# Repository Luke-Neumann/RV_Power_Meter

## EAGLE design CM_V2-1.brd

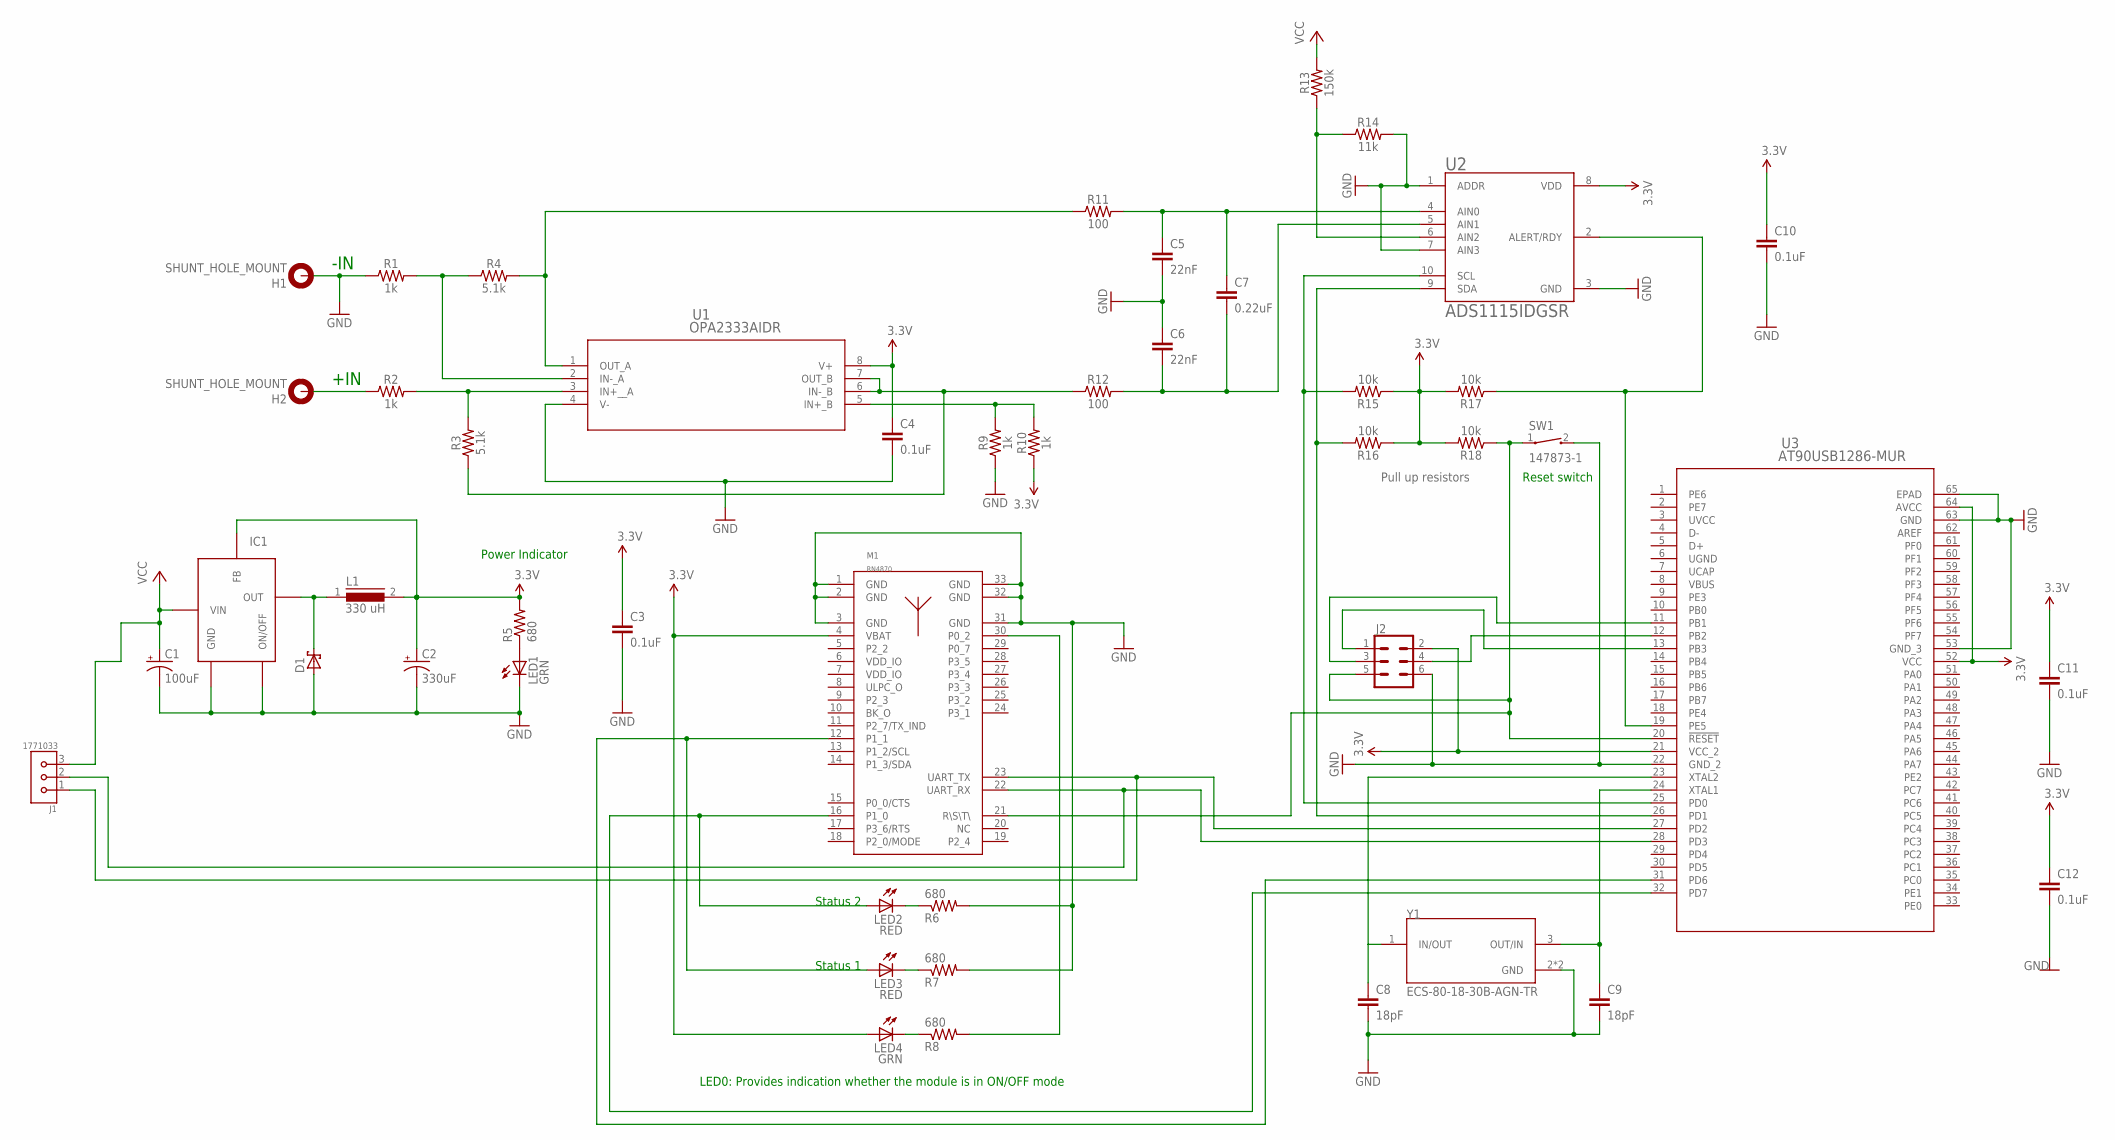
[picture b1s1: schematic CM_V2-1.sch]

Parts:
C1: 100uF; F_CAP; DIGIKEY# PCE3917CT-ND
C2: 330uF; F_CAP; DIGIKEY# PCE3401CT-ND
C3, C4, C10, C11, C12: 0.1uF; 0603
C5, C6: 22nF; 0603
C7: 0.22uF; 0603
C8, C9: 18pF; 0603
D1: SCHOTTKY_DIODE; SMD_DIODE
H1, H2: SHUNT_HOLE_MOUNT; 4,1-PAD
IC1: TL2575; TO-263-6
J1: 1771033; PHOENIX_1771033
J2: CONN_03X2FEMALE_SMD; 2X3_SMD
L1: 330 uH; DR125; DIGIKEY# SRR1208-102KLCT-ND
LED1, LED4: GRN; 0603_LED
LED2, LED3: RED; 0603_LED
M1: RN4870
R1, R2, R9, R10: 1k; 0603
R3, R4: 5.1k; 0603
R5, R6, R7, R8: 680; 0603_RESISTOR; DIGIKEY# P680GCT-ND
R11, R12: 100; 0603
R13: 150k; 0603
R14: 11k; 0603
R15, R16, R17, R18: 10k; 0603
SW1: 147873-1; SW_147873-1
U1: OPA2333AIDR; D8
U2: ADS1115IDGSR; SOP50P490X110-10N
U3: AT90USB1286-MUR; PS
Y1: ECS-80-18-30B-AGN-TR; XTAL_ECS-80-18-30B-AGN-TR

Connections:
3.3V: C2.+, C3.1, C4.1, C10.1, C11.1, C12.1, IC1.4 (FB), J2.2, L1.2, LED4.A, M1.4 (VBAT), R5.2, R10.1, R15.1, R16.1, R17.2, R18.2, U1.8 (V+), U2.8 (VDD), U3.21 (VCC_2), U3.52 (VCC), U3.64 (AVCC)
AREF: U3.62 (AREF)
GND: C1.-, C2.-, C3.2, C4.2, C5.2, C6.1, C8.2, C9.2, C10.2, C11.2, C12.2, D1.A, H1.B4,1, IC1.3 (GND), IC1.5 (ON/OFF), J2.6, LED1.C, M1.1 (GND), M1.2 (GND), M1.3 (GND), M1.31 (GND), M1.32 (GND), M1.33 (GND), R1.1, R6.2, R7.2, R9.1, R14.2, SW1.2, U1.4 (V-), U2.1 (ADDR), U2.3 (GND), U2.7 (AIN3), U3.22 (GND_2), U3.53 (GND_3), U3.63 (GND), U3.65 (EPAD), Y1.2 (GND), Y1.4 (GND)
unnamed: C5.1, C7.1, R11.2, U2.4 (AIN0)
unnamed: R9.2, R10.2, U1.5 (IN+_B)
unnamed: R15.2, U2.10 (SCL), U3.25 (PD0)
unnamed: R16.2, U2.9 (SDA), U3.26 (PD1)
unnamed: H2.B4,1, R2.1
unnamed: R4.2, R11.1, U1.1 (OUT_A)
unnamed: C6.2, C7.2, R12.2, U2.5 (AIN1)
unnamed: R1.2, R4.1, U1.2 (IN-_A)
unnamed: J1.2, M1.22 (UART_RX), U3.28 (PD3)
unnamed: J1.1, M1.23 (UART_TX), U3.27 (PD2)
unnamed: D1.C, IC1.2 (OUT), L1.1
unnamed: LED1.A, R5.1
unnamed: R2.2, R3.2, U1.3 (IN+__A)
unnamed: R3.1, R12.1, U1.6 (IN-_B), U1.7 (OUT_B)
unnamed: LED2.C, R6.1
unnamed: LED3.C, R7.1
unnamed: LED4.C, R8.1
unnamed: M1.30 (P0_2), R8.2
unnamed: LED3.A, M1.12 (P1_1), U3.31 (PD6)
unnamed: LED2.A, M1.16 (P1_0), U3.32 (PD7)
unnamed: J2.4, U3.12 (PB2)
unnamed: J2.1, U3.13 (PB3)
unnamed: J2.3, U3.11 (PB1)
unnamed: J2.5, M1.21 (R\S\T\), R18.1, SW1.1, U3.20 (!RESET)
unnamed: C8.1, U3.23 (XTAL2), Y1.1 (IN/OUT)
unnamed: C9.1, U3.24 (XTAL1), Y1.3 (OUT/IN)
unnamed: R17.1, U2.2 (ALERT/RDY), U3.19 (PE5)
unnamed: R13.1, R14.1, U2.6 (AIN2)
UGND: U3.6 (UGND)
UVCC: U3.3 (UVCC)
VBUS: U3.8 (VBUS)
VCC: C1.+, IC1.1 (VIN), J1.3, R13.2
VDD_IO: M1.6 (VDD_IO), M1.7 (VDD_IO)

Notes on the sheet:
+IN
-IN
Power Indicator
Status 1
Status 2
LED0: Provides indication whether the module is in ON/OFF mode
Reset switch
Pull up resistors

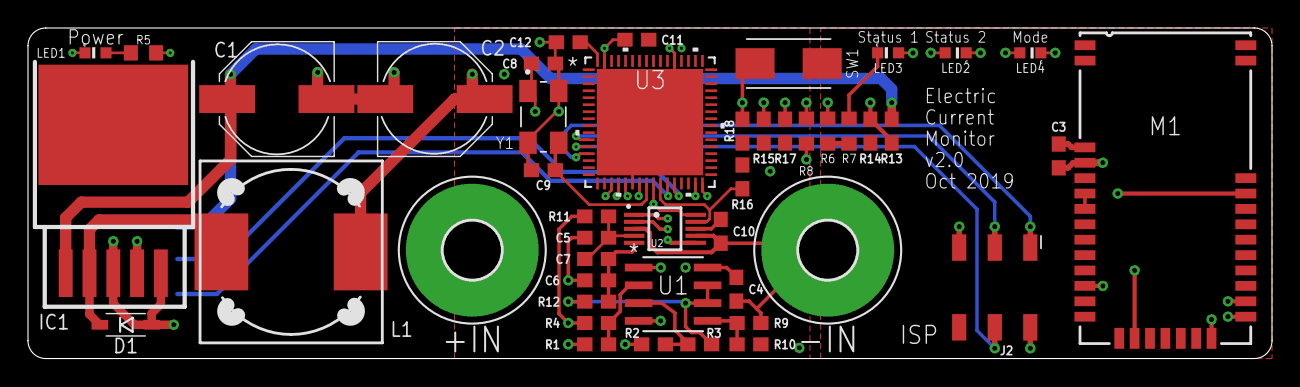
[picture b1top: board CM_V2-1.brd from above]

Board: 4 copper layers, 88.9 x 23.6 mm, 47 parts (1 on the bottom side), 32 nets.

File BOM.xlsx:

Qty | Parts | Value | DIGI-KEY_PART_NUMBER | Device | Package | Description | DESCRIPTION | DIGI-KEY_PURCHASE_URL
1 | J2 |  | 609-3487-1-ND | CONN_03X2FEMALE_SMD | 2X3_SMD | Multi connection point. Often used as Generic Header-pin footprint for 0.1 inch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
1 | D1 |  | 1N5819HW-FDICT-ND | SCHOTTKY_DIODE | SMD_DIODE
1 | IC1 |  | 296-21828-1-ND | TL2575 | TO-263-6
5 | C3, C4, C10, C11, C12 | 0.1uF | 1276-1000-1-ND | 0.1UF-0603-25V-5% | 603 | 0.1µF ceramic capacitors
1 | C7 | 0.22uF | 399-7884-1-ND | 0.22UF-0603-25V-10% | 603 | 0.22µF ceramic capacitors
2 | R11, R12 | 100 | P100DBCT-ND | 100OHM-0603-1/4W-5% | 603 | 100Ω resistor
1 | C1 | 100uF | PCE3917CT-ND | CAP_POLF | F_CAP
4 | R15, R16, R17, R18 | 10k | 311-10KDCT-ND | 10KOHM-0603-1/10W-1% | 603 | 10kΩ resistor
1 | R14 | 11k | P11KDBCT-ND | RESISTOR0603 | 603 | Generic Resistor Package
1 | SW1 | 147873-1 | EG4576CT-ND | 147873-1 | SW_147873-1 | Switch Tactile OFF (ON) SPST Rectangular Button J-Bend 0.05A 24VDC 1.77N SMD T/R | Switch Tactile OFF _ON_ SPST Rectangular Button J-Bend 0.05A 24VDC 1.77N SMD T/R
1 | R13 | 150k | P150KDBCT-ND | 150KOHM-0603-1/10W-1% | 603 | 150kΩ resistor
1 | J1 | 1771033 | 277-2066-1-ND | 1771033 | PHOENIX_1771033 | Fixed Miniature Connectors, Spring Cage, Horizontal, SMD, 3 Pos | Fixed Miniature Connectors, Spring Cage, Horizontal, SMD, 3 Pos | https://www.digikey.com/product-detail/en/phoenix-contact/17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
2 | C8, C9 | 18pF | 311-1061-1-ND | 18PF-0603-50V-5% | 603 | 18pF ceramic capacitors
4 | R1, R2, R9, R10 | 1k | P1.0KBECT-ND | 1KOHM-0603-1/10W-1% | 603 | 1kΩ resistor
2 | C5, C6 | 22nF | 399-9043-1-ND | 22NF/22,000PF-0603-50V-10% | 603 | 0.022uF/22nF/22,000pF ceramic capacitors
1 | L1 | 330 uH | SRR1208-331KLCT-ND | DR125 | DR125
1 | C2 | 330uF | PCE3401CT-ND | CAP_POLF | F_CAP
2 | R3, R4 | 5.1k | P5.1KBECT-ND | RESISTOR0603 | 603 | Generic Resistor Package
4 | R5, R6, R7, R8 | 680 | P680GCT-ND | RESISTOR0603 | 0603_RESISTOR
1 | U2 | ADS1115IDGSR | 296-38849-1-ND | ADS1115IDGSR | SOP50P490X110-10N | 16-Bit ADC with Integrated MUX, PGA, Comparator, Oscillator, and Reference 10-V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 | 16-Bit ADC with Integrated MUX, PGA, Comparator, Oscillator, and Reference 10-V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 | https://www.digikey.com/product-detail/en/texas-instruments/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
1 | U3 | AT90USB1286-MUR | AT90USB1286-MURCT-ND | AT90USB1286-MUR | PS
1 | Y1 | ECS-80-18-30B-AGN-TR | XC2709CT-ND | ECS-80-18-30B-AGN-TR | XTAL_ECS-80-18-30B-AGN-TR | The ECX-53B is a miniature SMD Crystal with a 3.2 x 5 mm | Crystal 8MHz ±25ppm _Tol_ ±30ppm _Stability_ 18pF FUND 100Ohm 4-Pin Mini-SMD T/R | https://www.digikey.com/product-detail/en/ecs-inc/ECS-80-18-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
 | LED2, LED3 | RED | 516-3074-1-ND | LED0603 | 0603_LED
4 | LED1, LED4 | GRN | 516-2493-1-ND | LED0603 | 0603_LED
1 | U1 | OPA2333AIDR | 296-26249-1-ND | OPA2333AIDR | D8
1 | M1 | RN4870 | RN4870-1/RM130-ND | RN4870 | RN4870

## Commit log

2019-11-22 Create Board_Design_Files

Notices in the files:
parts and their libraries:
SparkFun-Capacitors: Licensing: Creative Commons ShareAlike 4.0 International - https://creativecommons.org/licenses/by-sa/4.0
SparkFun-Aesthetics: Licensing: CC v3.0 Share-Alike You are welcome to use this library for commercial purposes.
